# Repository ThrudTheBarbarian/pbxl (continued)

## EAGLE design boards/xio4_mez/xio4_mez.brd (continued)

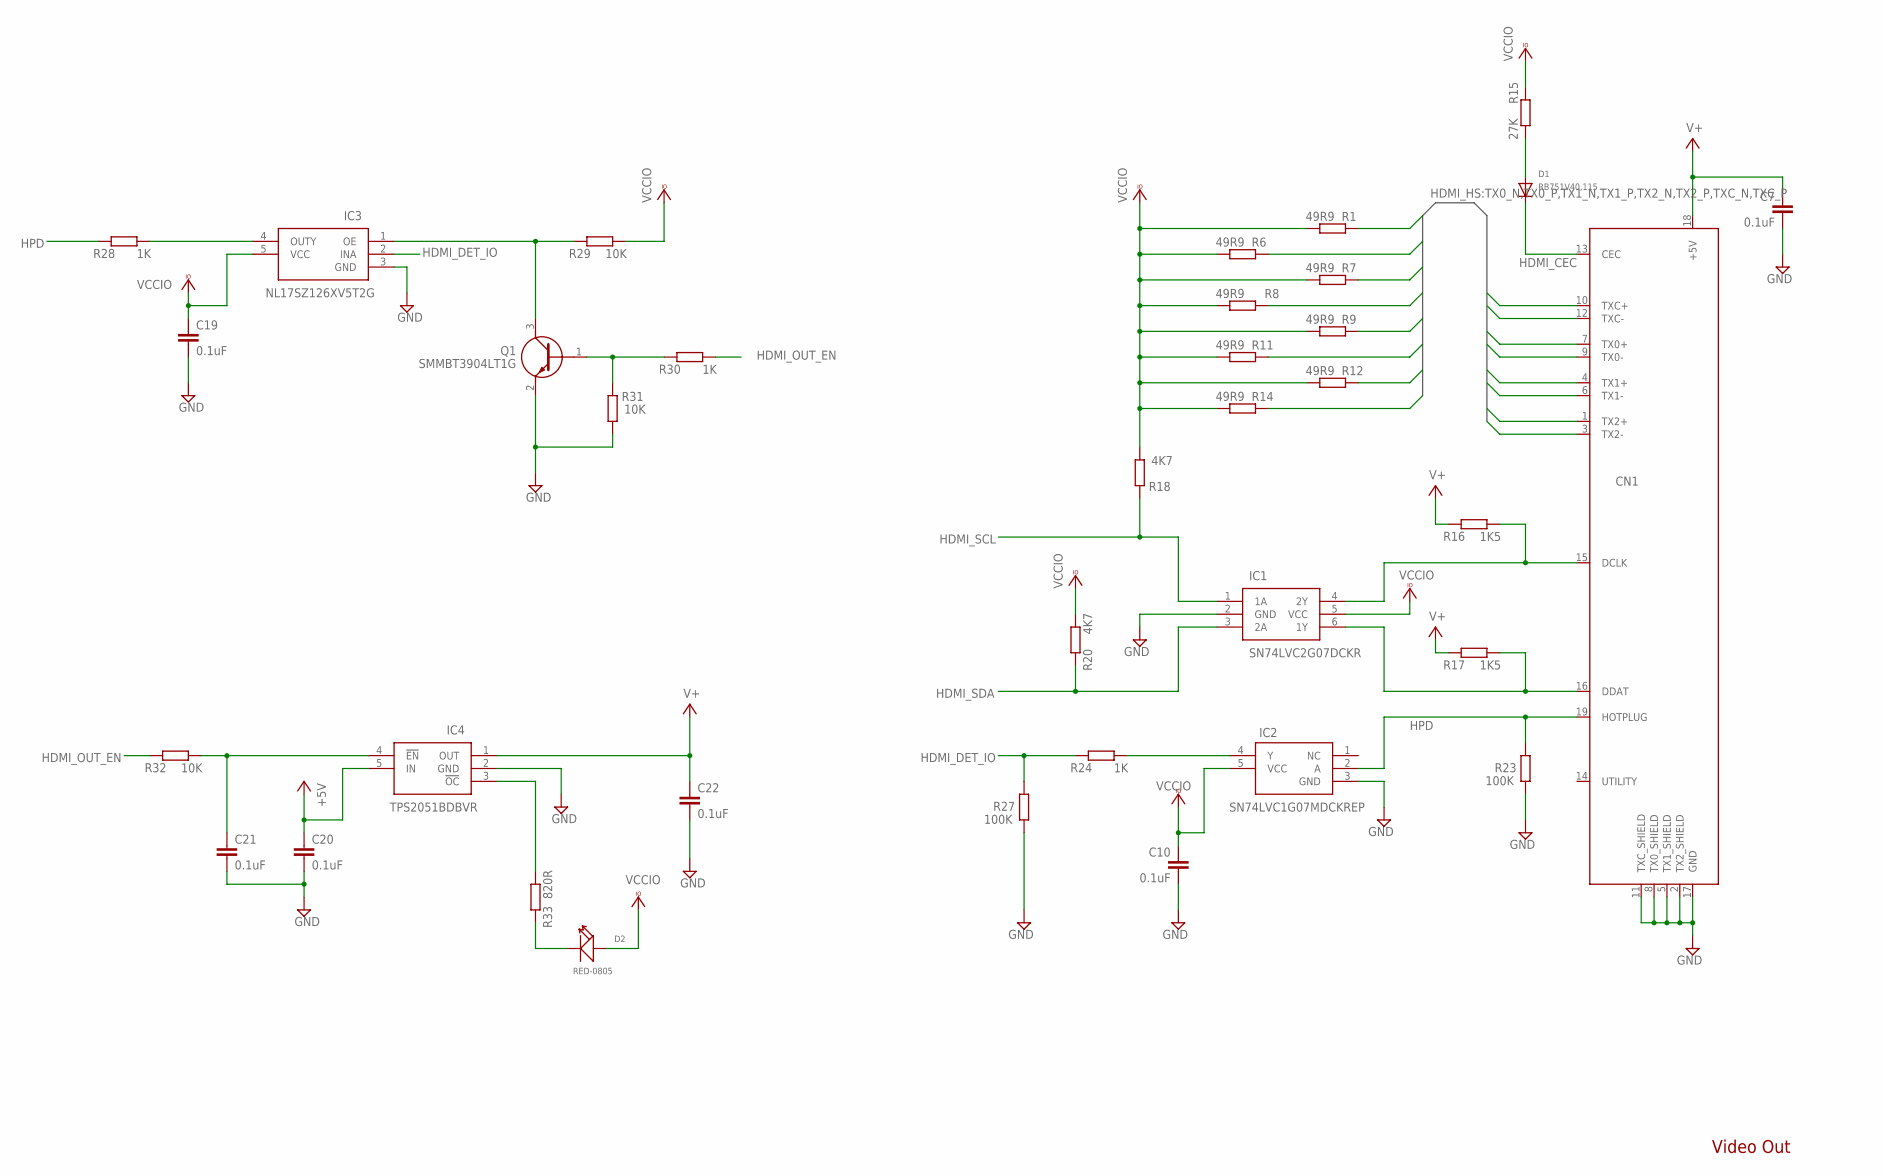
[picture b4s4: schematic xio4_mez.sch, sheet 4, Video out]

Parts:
C7, C10, C19, C20, C21, C22: 0.1uF; C0201
CN1: HDMI_MOLEX_47151-0001
D1: RB751V40,115; SOD-323
D2: RED-0805; LED-0805
IC1: SN74LVC2G07DCKR; SOT65P210X110X6N
IC2: SN74LVC1G07MDCKREP; SOT65P210X110-5N
IC3: NL17SZ126XV5T2G; SOTFL50P160X60-5N
IC4: TPS2051BDBVR; SOT95P280X145-5N
Q1: SMMBT3904LT1G; SOT96P237X111-3N
R1, R6, R7, R8, R9, R11, R12, R14: 49R9; R0201
R15: 27K; R0201
R16, R17: 1K5; R0201
R18, R20: 4K7; R0201
R23, R27: 100K; R0201
R24, R28, R30: 1K; R0201
R29, R31, R32: 10K; R0201
R33: 820R; R0201

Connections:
+5V: C20.1, IC4.5 (IN); also elsewhere on the board
GND: C7.2, C10.2, C19.2, C20.2, C21.2, C22.2, CN1.2 (TX2_SHIELD), CN1.5 (TX1_SHIELD), CN1.8 (TX0_SHIELD), CN1.11 (TXC_SHIELD), CN1.17 (GND), CN1.P$1 (GND), CN1.P$2 (GND), CN1.P$3 (GND), CN1.P$4 (GND), IC1.2 (GND), IC2.3 (GND), IC3.3 (GND), IC4.2 (GND), Q1.2 (E), R23.1, R27.1, R31.2; also elsewhere on the board
HDMI_CEC: CN1.13 (CEC), D1.C
HDMI_DET_IO: IC3.2 (INA), R24.2, R27.2; also elsewhere on the board
HDMI_OUT_EN: R30.1, R32.2; also elsewhere on the board
HDMI_SCL: IC1.1 (1A), R18.2; also elsewhere on the board
HDMI_SDA: IC1.3 (2A), R20.2; also elsewhere on the board
HPD: CN1.19 (HOTPLUG), IC2.2 (A), R23.2, R28.2
unnamed: CN1.16 (DDAT), IC1.6 (1Y), R17.1
unnamed: D1.A, R15.1
unnamed: CN1.15 (DCLK), IC1.4 (2Y), R16.1
unnamed: IC3.1 (OE), Q1.3 (C), R29.2
unnamed: IC2.4 (Y), R24.1
unnamed: IC3.4 (OUTY), R28.1
unnamed: Q1.1 (B), R30.2, R31.1
unnamed: C21.1, IC4.4 (!EN), R32.1
unnamed: IC4.3 (!OC), R33.1
unnamed: D2.-, R33.2
TX0_N: CN1.9 (TX0-), R1.2; also elsewhere on the board
TX0_P: CN1.7 (TX0+), R6.2; also elsewhere on the board
TX1_N: CN1.6 (TX1-), R7.2; also elsewhere on the board
TX1_P: CN1.4 (TX1+), R8.2; also elsewhere on the board
TX2_N: CN1.3 (TX2-), R9.2; also elsewhere on the board
TX2_P: CN1.1 (TX2+), R11.2; also elsewhere on the board
TXC_N: CN1.12 (TXC-), R12.2; also elsewhere on the board
TXC_P: CN1.10 (TXC+), R14.2; also elsewhere on the board
V+: C7.1, C22.1, CN1.18 (+5V), IC4.1 (OUT), R16.2, R17.2
VCCIO: C10.1, C19.1, D2.+, IC1.5 (VCC), IC2.5 (VCC), IC3.5 (VCC), R1.1, R6.1, R7.1, R8.1, R9.1, R11.1, R12.1, R14.1, R15.2, R18.1, R20.1, R29.1; also elsewhere on the board

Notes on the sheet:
Video Out

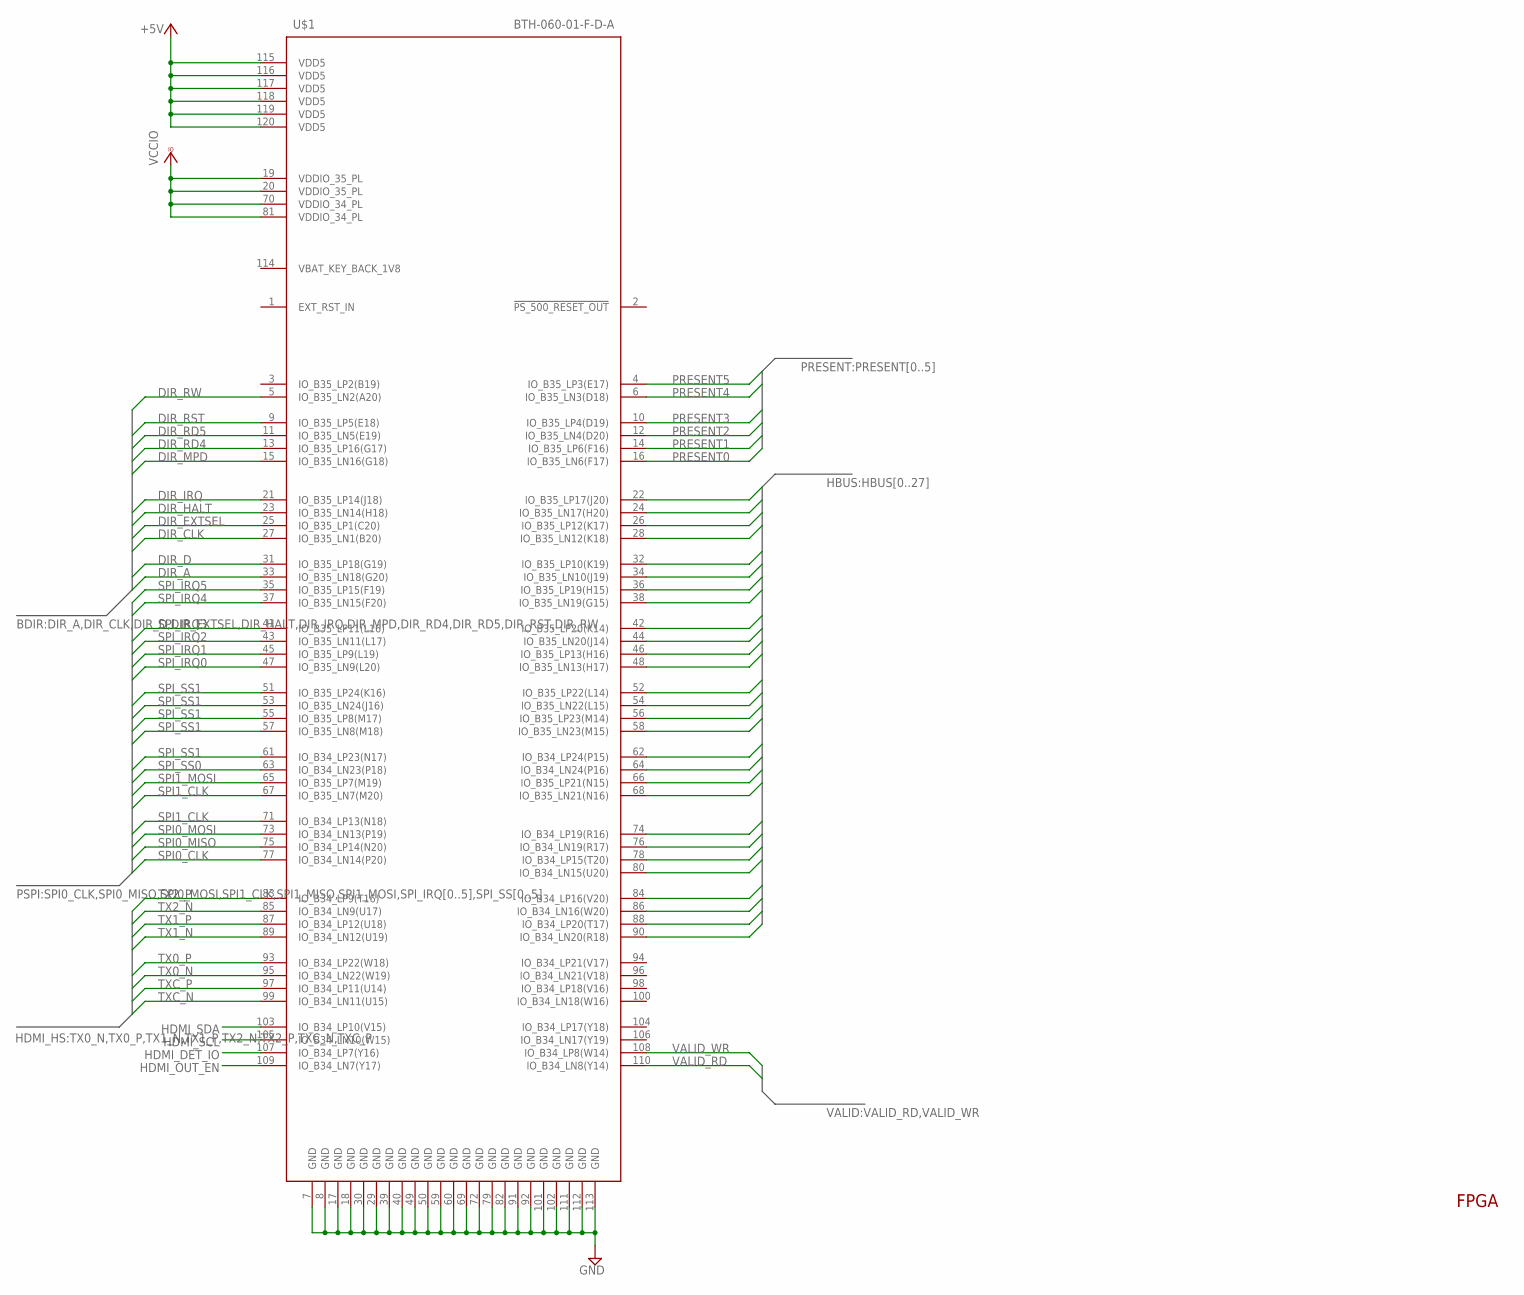
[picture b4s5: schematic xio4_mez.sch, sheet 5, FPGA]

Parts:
U$1: BTH-060-01-F-D-A

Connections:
+5V: U$1.115 (VDD5), U$1.116 (VDD5), U$1.117 (VDD5), U$1.118 (VDD5), U$1.119 (VDD5), U$1.120 (VDD5); also elsewhere on the board
DIR_A: U$1.33 (IO_B35_LN18(G20)); also elsewhere on the board
DIR_CLK: U$1.27 (IO_B35_LN1(B20)); also elsewhere on the board
DIR_D: U$1.31 (IO_B35_LP18(G19)); also elsewhere on the board
DIR_EXTSEL: U$1.25 (IO_B35_LP1(C20)); also elsewhere on the board
DIR_HALT: U$1.23 (IO_B35_LN14(H18)); also elsewhere on the board
DIR_IRQ: U$1.21 (IO_B35_LP14(J18)); also elsewhere on the board
DIR_MPD: U$1.15 (IO_B35_LN16(G18)); also elsewhere on the board
DIR_RD4: U$1.13 (IO_B35_LP16(G17)); also elsewhere on the board
DIR_RD5: U$1.11 (IO_B35_LN5(E19)); also elsewhere on the board
DIR_RST: U$1.9 (IO_B35_LP5(E18)); also elsewhere on the board
DIR_RW: U$1.5 (IO_B35_LN2(A20)); also elsewhere on the board
GND: U$1.7 (GND), U$1.8 (GND), U$1.17 (GND), U$1.18 (GND), U$1.29 (GND), U$1.30 (GND), U$1.39 (GND), U$1.40 (GND), U$1.49 (GND), U$1.50 (GND), U$1.59 (GND), U$1.60 (GND), U$1.69 (GND), U$1.72 (GND), U$1.79 (GND), U$1.82 (GND), U$1.91 (GND), U$1.92 (GND), U$1.101 (GND), U$1.102 (GND), U$1.111 (GND), U$1.112 (GND), U$1.113 (GND); also elsewhere on the board
HBUS0: U$1.22 (IO_B35_LP17(J20)); also elsewhere on the board
HBUS1: U$1.24 (IO_B35_LN17(H20)); also elsewhere on the board
HBUS2: U$1.26 (IO_B35_LP12(K17)); also elsewhere on the board
HBUS3: U$1.28 (IO_B35_LN12(K18)); also elsewhere on the board
HBUS4: U$1.32 (IO_B35_LP10(K19)); also elsewhere on the board
HBUS5: U$1.34 (IO_B35_LN10(J19)); also elsewhere on the board
HBUS6: U$1.36 (IO_B35_LP19(H15)); also elsewhere on the board
HBUS7: U$1.38 (IO_B35_LN19(G15)); also elsewhere on the board
HBUS8: U$1.42 (IO_B35_LP20(K14)); also elsewhere on the board
HBUS9: U$1.44 (IO_B35_LN20(J14)); also elsewhere on the board
HBUS10: U$1.46 (IO_B35_LP13(H16)); also elsewhere on the board
HBUS11: U$1.48 (IO_B35_LN13(H17)); also elsewhere on the board
HBUS12: U$1.52 (IO_B35_LP22(L14)); also elsewhere on the board
HBUS13: U$1.54 (IO_B35_LN22(L15)); also elsewhere on the board
HBUS14: U$1.56 (IO_B35_LP23(M14)); also elsewhere on the board
HBUS15: U$1.58 (IO_B35_LN23(M15)); also elsewhere on the board
HBUS16: U$1.62 (IO_B34_LP24(P15)); also elsewhere on the board
HBUS17: U$1.64 (IO_B34_LN24(P16)); also elsewhere on the board
HBUS18: U$1.66 (IO_B35_LP21(N15)); also elsewhere on the board
HBUS19: U$1.68 (IO_B35_LN21(N16)); also elsewhere on the board
HBUS20: U$1.74 (IO_B34_LP19(R16)); also elsewhere on the board
HBUS21: U$1.76 (IO_B34_LN19(R17)); also elsewhere on the board
HBUS22: U$1.78 (IO_B34_LP15(T20)); also elsewhere on the board
HBUS23: U$1.80 (IO_B34_LN15(U20)); also elsewhere on the board
HBUS24: U$1.84 (IO_B34_LP16(V20)); also elsewhere on the board
HBUS25: U$1.86 (IO_B34_LN16(W20)); also elsewhere on the board
HBUS26: U$1.88 (IO_B34_LP20(T17)); also elsewhere on the board
HBUS27: U$1.90 (IO_B34_LN20(R18)); also elsewhere on the board
HDMI_DET_IO: U$1.107 (IO_B34_LP7(Y16)); also elsewhere on the board
HDMI_OUT_EN: U$1.109 (IO_B34_LN7(Y17)); also elsewhere on the board
HDMI_SCL: U$1.105 (IO_B34_LN10(W15)); also elsewhere on the board
HDMI_SDA: U$1.103 (IO_B34_LP10(V15)); also elsewhere on the board
PRESENT0: U$1.16 (IO_B35_LN6(F17)); also elsewhere on the board
PRESENT1: U$1.14 (IO_B35_LP6(F16)); also elsewhere on the board
PRESENT2: U$1.12 (IO_B35_LN4(D20)); also elsewhere on the board
PRESENT3: U$1.10 (IO_B35_LP4(D19)); also elsewhere on the board
PRESENT4: U$1.6 (IO_B35_LN3(D18)); also elsewhere on the board
PRESENT5: U$1.4 (IO_B35_LP3(E17)); also elsewhere on the board
SPI0_CLK: U$1.77 (IO_B34_LN14(P20)); also elsewhere on the board
SPI0_MISO: U$1.75 (IO_B34_LP14(N20)); also elsewhere on the board
SPI0_MOSI: U$1.73 (IO_B34_LN13(P19)); also elsewhere on the board
SPI1_CLK: U$1.71 (IO_B34_LP13(N18)); also elsewhere on the board
SPI1_MISO: U$1.67 (IO_B35_LN7(M20)); also elsewhere on the board
SPI1_MOSI: U$1.65 (IO_B35_LP7(M19)); also elsewhere on the board
SPI_IRQ0: U$1.47 (IO_B35_LN9(L20)); also elsewhere on the board
SPI_IRQ1: U$1.45 (IO_B35_LP9(L19)); also elsewhere on the board
SPI_IRQ2: U$1.43 (IO_B35_LN11(L17)); also elsewhere on the board
SPI_IRQ3: U$1.41 (IO_B35_LP11(L16)); also elsewhere on the board
SPI_IRQ4: U$1.37 (IO_B35_LN15(F20)); also elsewhere on the board
SPI_IRQ5: U$1.35 (IO_B35_LP15(F19)); also elsewhere on the board
SPI_SS0: U$1.63 (IO_B34_LN23(P18)); also elsewhere on the board
SPI_SS1: U$1.61 (IO_B34_LP23(N17)); also elsewhere on the board
SPI_SS2: U$1.57 (IO_B35_LN8(M18)); also elsewhere on the board
SPI_SS3: U$1.55 (IO_B35_LP8(M17)); also elsewhere on the board
SPI_SS4: U$1.53 (IO_B35_LN24(J16)); also elsewhere on the board
SPI_SS5: U$1.51 (IO_B35_LP24(K16)); also elsewhere on the board
TX0_N: U$1.95 (IO_B34_LN22(W19)); also elsewhere on the board
TX0_P: U$1.93 (IO_B34_LP22(W18)); also elsewhere on the board
TX1_N: U$1.89 (IO_B34_LN12(U19)); also elsewhere on the board
TX1_P: U$1.87 (IO_B34_LP12(U18)); also elsewhere on the board
TX2_N: U$1.85 (IO_B34_LN9(U17)); also elsewhere on the board
TX2_P: U$1.83 (IO_B34_LP9(T16)); also elsewhere on the board
TXC_N: U$1.99 (IO_B34_LN11(U15)); also elsewhere on the board
TXC_P: U$1.97 (IO_B34_LP11(U14)); also elsewhere on the board
VALID_RD: U$1.110 (IO_B34_LN8(Y14)); also elsewhere on the board
VALID_WR: U$1.108 (IO_B34_LP8(W14)); also elsewhere on the board
VCCIO: U$1.19 (VDDIO_35_PL), U$1.20 (VDDIO_35_PL), U$1.70 (VDDIO_34_PL), U$1.81 (VDDIO_34_PL); also elsewhere on the board

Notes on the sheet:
FPGA

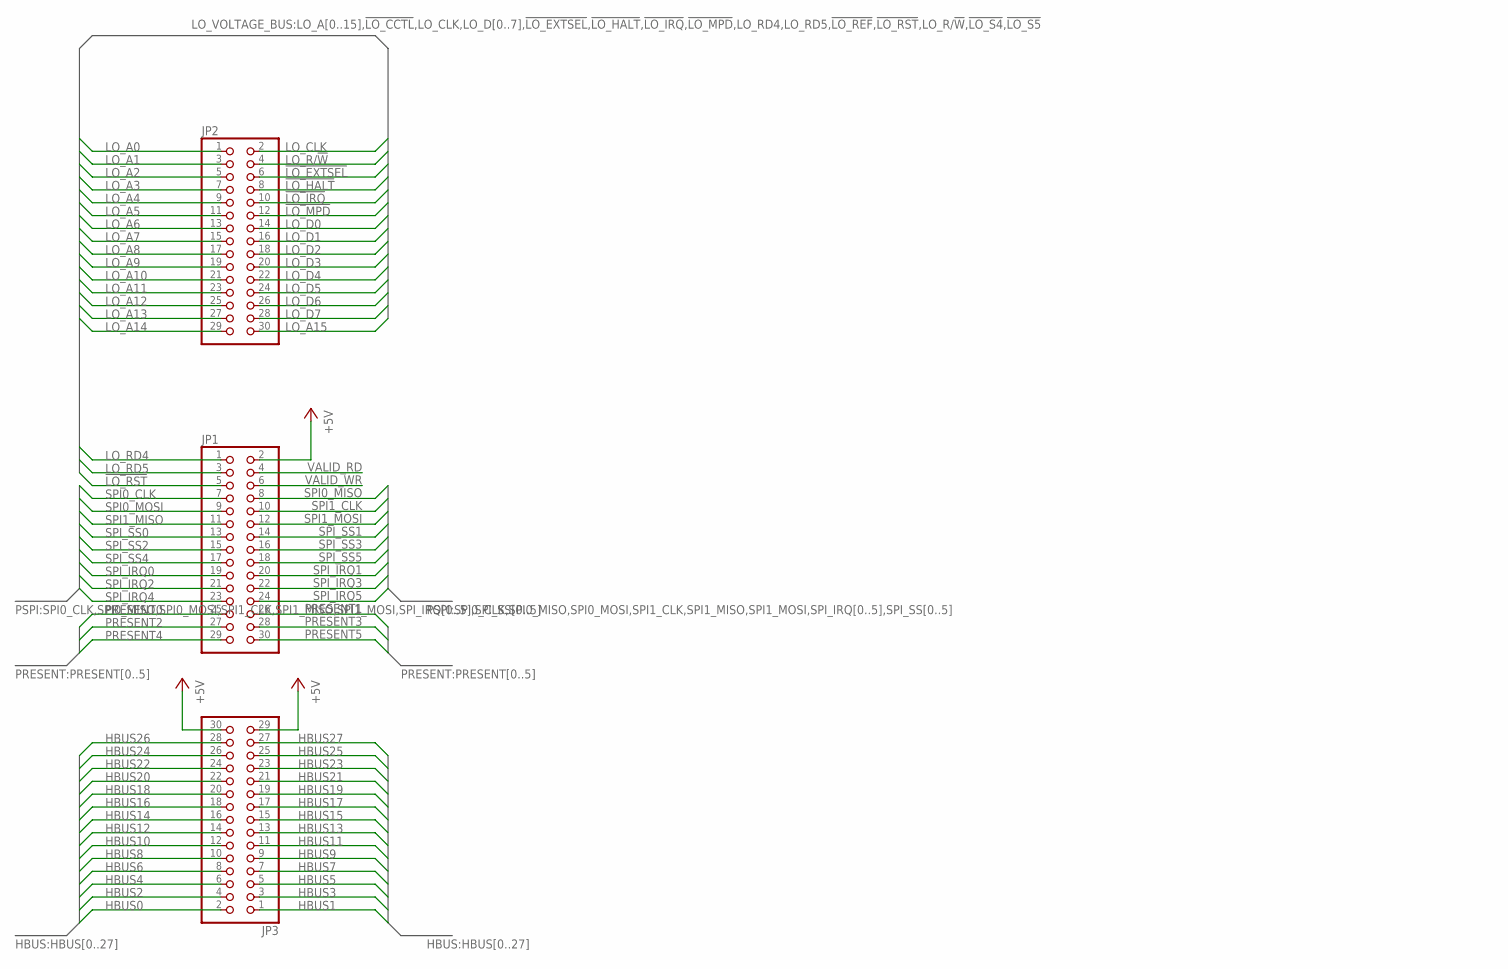
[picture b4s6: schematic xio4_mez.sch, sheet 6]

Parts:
JP1, JP2, JP3: PINHD-2X15_2.54-SMD; 2X15SMD

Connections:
!LO_EXTSEL!: JP2.6; also elsewhere on the board
!LO_HALT!: JP2.8; also elsewhere on the board
!LO_IRQ!: JP2.10; also elsewhere on the board
!LO_MPD!: JP2.12; also elsewhere on the board
!LO_RST!: JP1.5; also elsewhere on the board
+5V: JP1.2, JP3.29, JP3.30; also elsewhere on the board
HBUS0: JP3.2; also elsewhere on the board
HBUS1: JP3.1; also elsewhere on the board
HBUS2: JP3.4; also elsewhere on the board
HBUS3: JP3.3; also elsewhere on the board
HBUS4: JP3.6; also elsewhere on the board
HBUS5: JP3.5; also elsewhere on the board
HBUS6: JP3.8; also elsewhere on the board
HBUS7: JP3.7; also elsewhere on the board
HBUS8: JP3.10; also elsewhere on the board
HBUS9: JP3.9; also elsewhere on the board
HBUS10: JP3.12; also elsewhere on the board
HBUS11: JP3.11; also elsewhere on the board
HBUS12: JP3.14; also elsewhere on the board
HBUS13: JP3.13; also elsewhere on the board
HBUS14: JP3.16; also elsewhere on the board
HBUS15: JP3.15; also elsewhere on the board
HBUS16: JP3.18; also elsewhere on the board
HBUS17: JP3.17; also elsewhere on the board
HBUS18: JP3.20; also elsewhere on the board
HBUS19: JP3.19; also elsewhere on the board
HBUS20: JP3.22; also elsewhere on the board
HBUS21: JP3.21; also elsewhere on the board
HBUS22: JP3.24; also elsewhere on the board
HBUS23: JP3.23; also elsewhere on the board
HBUS24: JP3.26; also elsewhere on the board
HBUS25: JP3.25; also elsewhere on the board
HBUS26: JP3.28; also elsewhere on the board
HBUS27: JP3.27; also elsewhere on the board
LO_A0: JP2.1; also elsewhere on the board
LO_A1: JP2.3; also elsewhere on the board
LO_A2: JP2.5; also elsewhere on the board
LO_A3: JP2.7; also elsewhere on the board
LO_A4: JP2.9; also elsewhere on the board
LO_A5: JP2.11; also elsewhere on the board
LO_A6: JP2.13; also elsewhere on the board
LO_A7: JP2.15; also elsewhere on the board
LO_A8: JP2.17; also elsewhere on the board
LO_A9: JP2.19; also elsewhere on the board
LO_A10: JP2.21; also elsewhere on the board
LO_A11: JP2.23; also elsewhere on the board
LO_A12: JP2.25; also elsewhere on the board
LO_A13: JP2.27; also elsewhere on the board
LO_A14: JP2.29; also elsewhere on the board
LO_A15: JP2.30; also elsewhere on the board
LO_CLK: JP2.2; also elsewhere on the board
LO_D0: JP2.14; also elsewhere on the board
LO_D1: JP2.16; also elsewhere on the board
LO_D2: JP2.18; also elsewhere on the board
LO_D3: JP2.20; also elsewhere on the board
LO_D4: JP2.22; also elsewhere on the board
LO_D5: JP2.24; also elsewhere on the board
LO_D6: JP2.26; also elsewhere on the board
LO_D7: JP2.28; also elsewhere on the board
LO_R/!W!: JP2.4; also elsewhere on the board
LO_RD4: JP1.1; also elsewhere on the board
LO_RD5: JP1.3; also elsewhere on the board
PRESENT0: JP1.25; also elsewhere on the board
PRESENT1: JP1.26; also elsewhere on the board
PRESENT2: JP1.27; also elsewhere on the board
PRESENT3: JP1.28; also elsewhere on the board
PRESENT4: JP1.29; also elsewhere on the board
PRESENT5: JP1.30; also elsewhere on the board
SPI0_CLK: JP1.7; also elsewhere on the board
SPI0_MISO: JP1.8; also elsewhere on the board
SPI0_MOSI: JP1.9; also elsewhere on the board
SPI1_CLK: JP1.10; also elsewhere on the board
SPI1_MISO: JP1.11; also elsewhere on the board
SPI1_MOSI: JP1.12; also elsewhere on the board
SPI_IRQ0: JP1.19; also elsewhere on the board
SPI_IRQ1: JP1.20; also elsewhere on the board
SPI_IRQ2: JP1.21; also elsewhere on the board
SPI_IRQ3: JP1.22; also elsewhere on the board
SPI_IRQ4: JP1.23; also elsewhere on the board
SPI_IRQ5: JP1.24; also elsewhere on the board
SPI_SS0: JP1.13; also elsewhere on the board
SPI_SS1: JP1.14; also elsewhere on the board
SPI_SS2: JP1.15; also elsewhere on the board
SPI_SS3: JP1.16; also elsewhere on the board
SPI_SS4: JP1.17; also elsewhere on the board
SPI_SS5: JP1.18; also elsewhere on the board
VALID_RD: JP1.4; also elsewhere on the board
VALID_WR: JP1.6; also elsewhere on the board

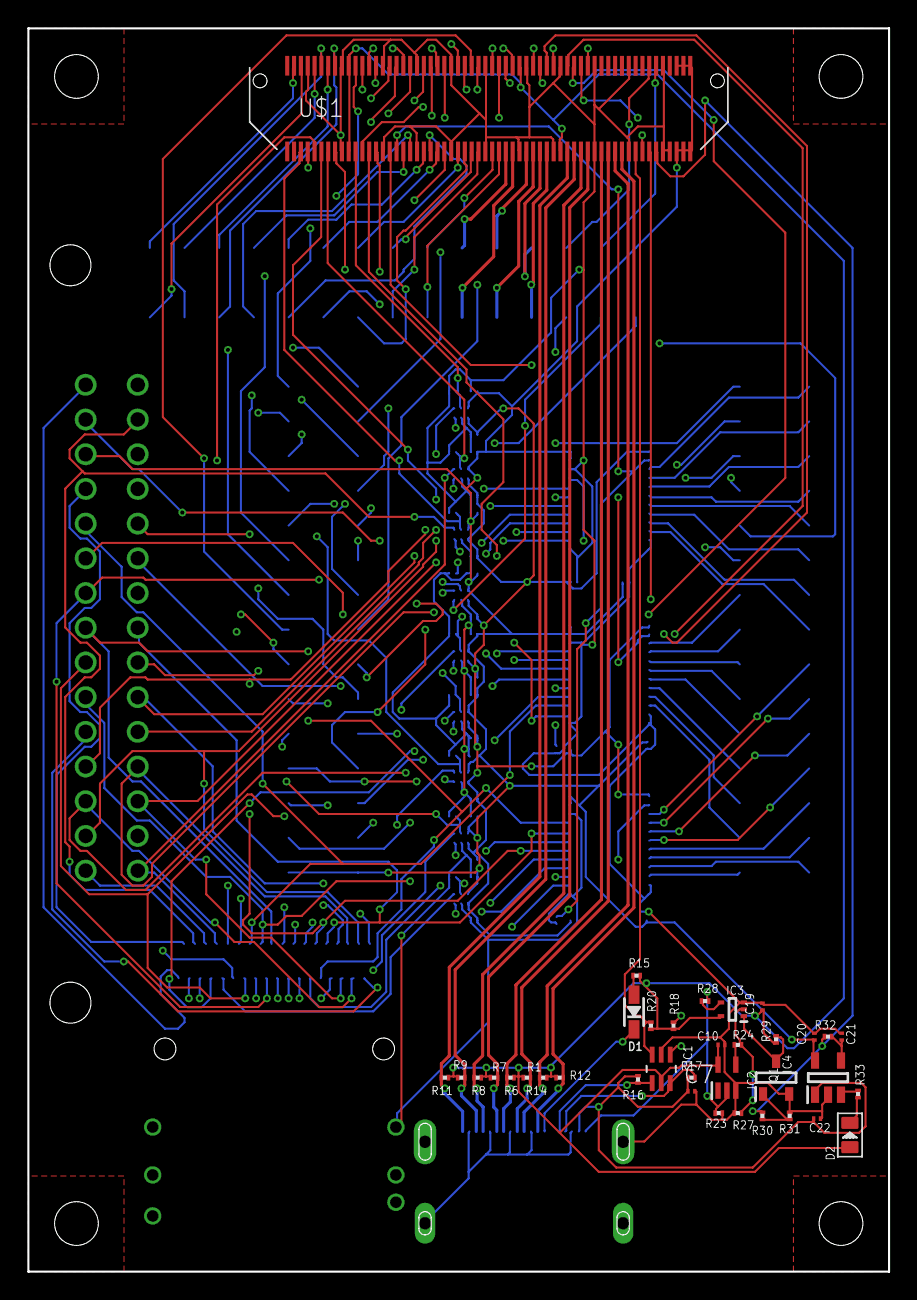
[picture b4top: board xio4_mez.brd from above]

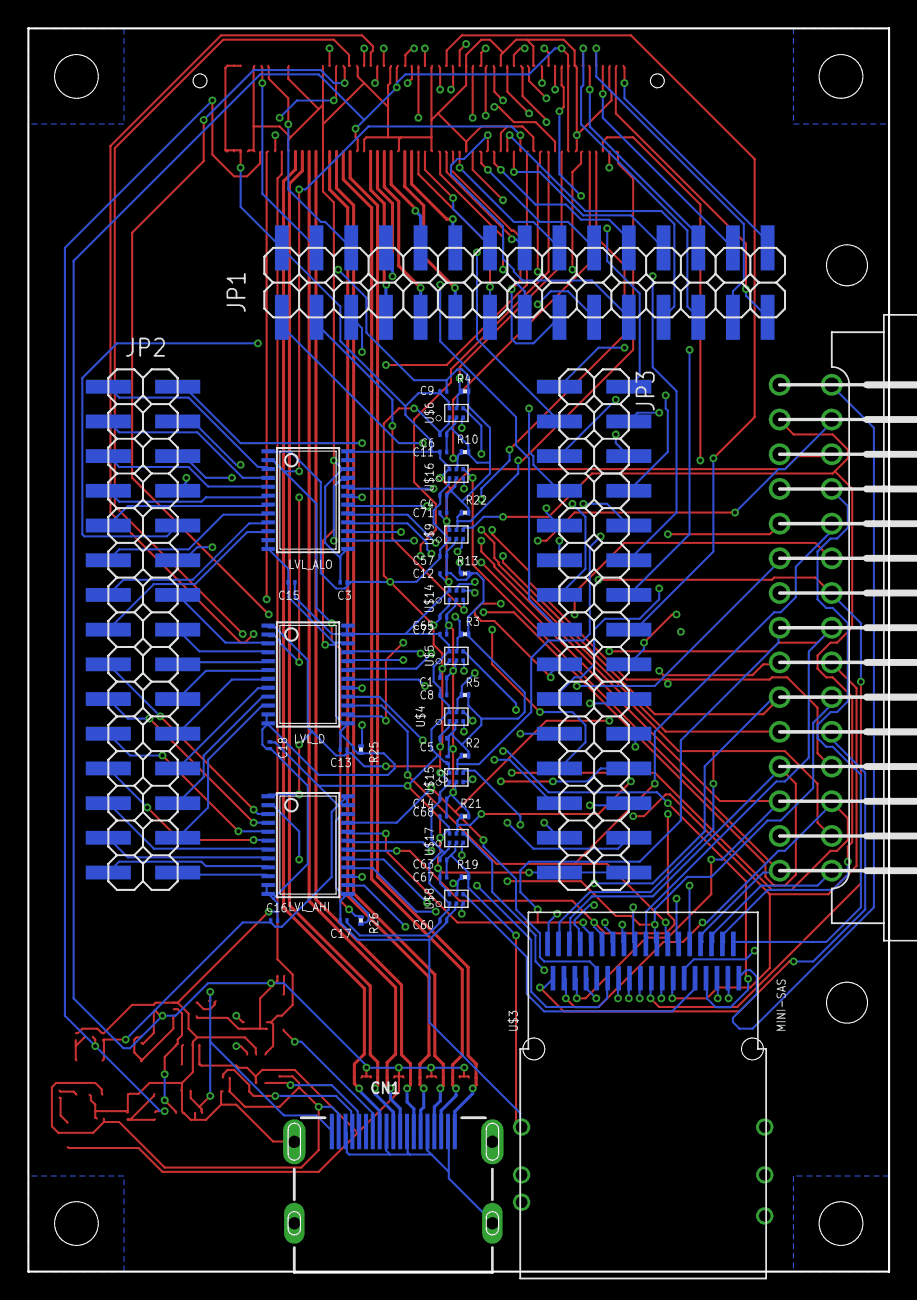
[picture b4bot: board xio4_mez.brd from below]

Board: 4 copper layers, 63.0 x 91.0 mm, 89 parts (53 on the bottom side), 163 nets.

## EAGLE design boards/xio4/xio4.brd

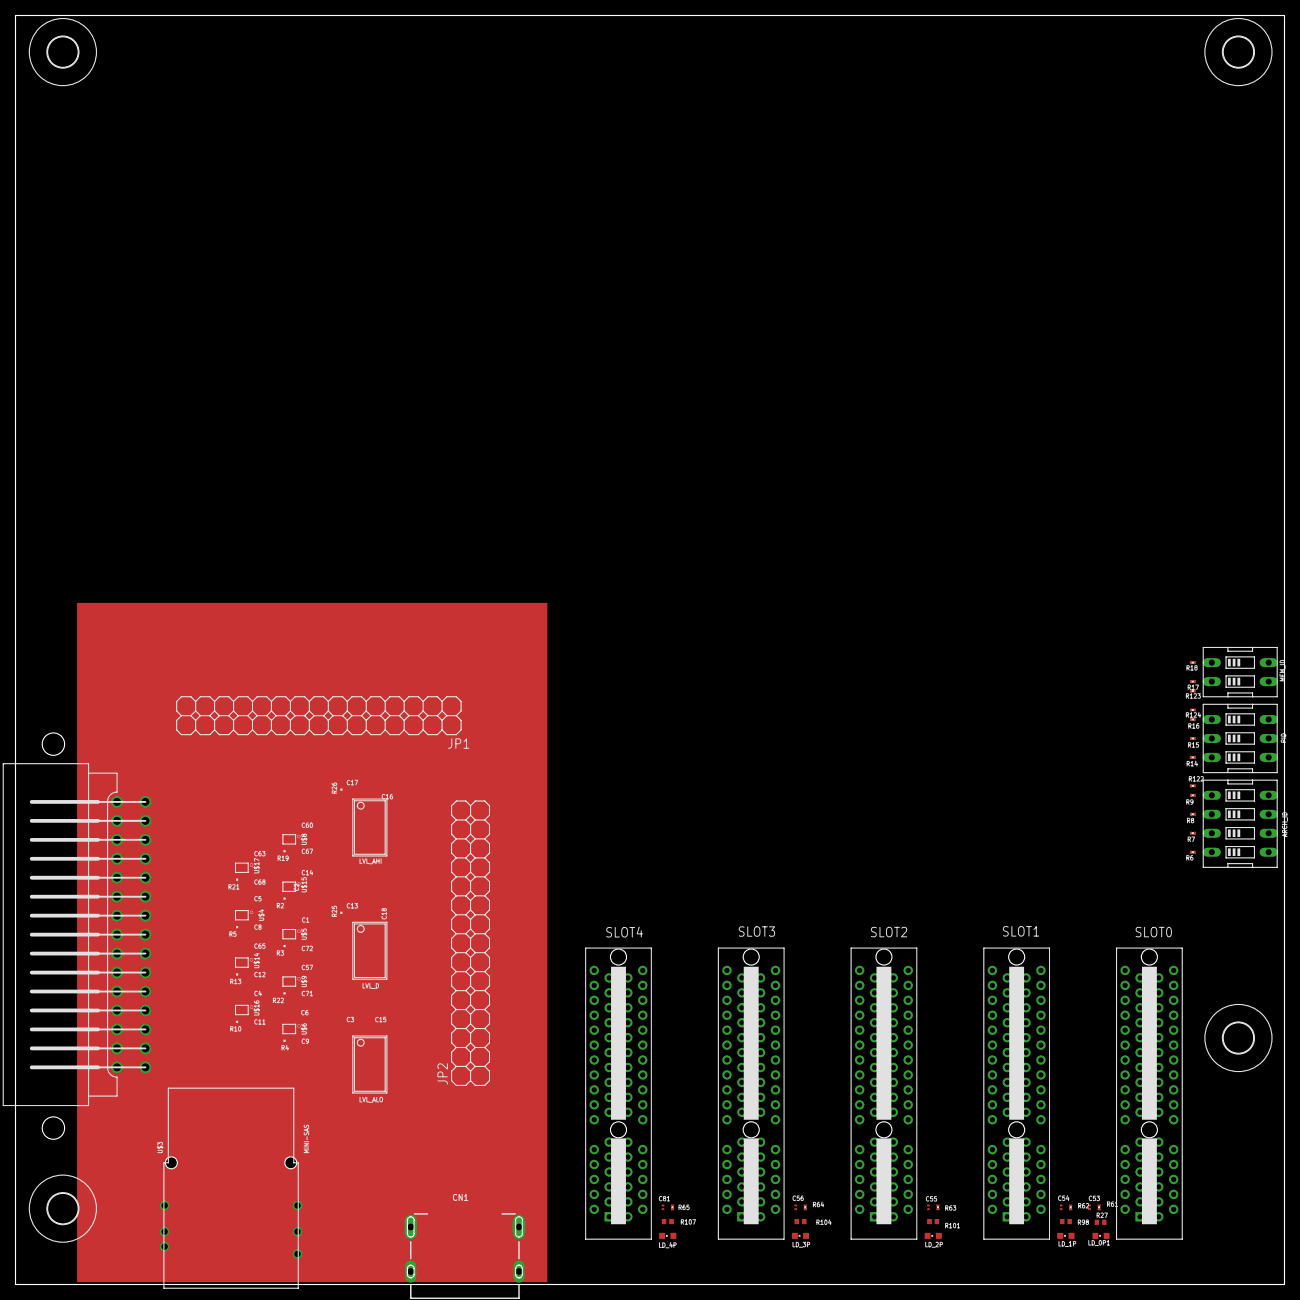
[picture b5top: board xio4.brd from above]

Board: 4 copper layers, 170.0 x 170.0 mm, 96 parts (0 on the bottom side), 123 nets, no tracks yet.

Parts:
ARCH_ID: 209-4MS; EDG-04
C1, C2, C3, C4, C5, C6, C8, C9, C11, C12, C13, C14, C15, C16, C17, C18, C53, C54, C55, C56, C57, C60, C63, C65, C67, C68, C71, C72, C81: 0.1uF; C0201
CARTRIDGE: 5650118-1; A8_CART
CN1: HDMI_MOLEX_47151-0001
H3, H6, H7, H8: MOUNT-HOLE4.1; 4,1
JP1, JP2: 2X15SMD
LD_0P1, LD_1P, LD_2P, LD_3P, LD_4P: SML-D12D1WT86; CHIPLED_0603
LVL_AHI: SN74LVC8T245; TSSOP24
LVL_ALO: SN74LVC8T245; TSSOP24
LVL_D: SN74LVC8T245; TSSOP24
MEM_ID: 209-2MS; EDG-02
PID: 209-3MS; EDG-03
R2, R3, R4, R5, R10, R13, R19, R21, R22, R25, R26, R61, R62, R63, R64, R65: 10K; R0201
R6, R7, R8, R9, R14, R15, R16, R17, R18: 47K; R0201
R27, R98, R101, R104, R107: 59R; R0402
R122, R123, R124: 1K; R0201
SLOT0, SLOT1, SLOT2, SLOT3, SLOT4: PCIE_64; PCI-E_64
U$3: MINI-SAS
U$4, U$5, U$6, U$8, U$9, U$14, U$15, U$16, U$17: 74LVC1T45GWSOT866; SOT886

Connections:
!HI_CCTL!: CARTRIDGE.P15, U$3.PA18
!HI_EXTSEL!: U$3.PB13, U$5.4
!HI_HALT!: U$3.PA14, U$8.4
!HI_IRQ!: U$3.PB14, U$6.4
!HI_MPD!: U$3.PA15, U$4.4
!HI_RST!: U$3.PA17, U$17.4
!HI_S4!: CARTRIDGE.P1, U$3.PB16
!HI_S5!: CARTRIDGE.P12, U$3.PB18
!LO_CCTL!: SLOT0.A27, SLOT1.A27, SLOT2.A27, SLOT3.A27, SLOT4.A27
!LO_EXTSEL!: SLOT0.A29, SLOT1.A29, SLOT2.A29, SLOT3.A29, SLOT4.A29, U$5.3
!LO_HALT!: SLOT0.B13, SLOT1.B13, SLOT2.B13, SLOT3.B13, SLOT4.B13, U$8.3
!LO_IRQ!: SLOT0.B14, SLOT1.B14, SLOT2.B14, SLOT3.B14, SLOT4.B14, U$6.3
!LO_MPD!: SLOT0.A30, SLOT1.A30, SLOT2.A30, SLOT3.A30, SLOT4.A30, U$4.3
!LO_REF!: SLOT0.B15, SLOT1.B15, SLOT2.B15, SLOT3.B15, SLOT4.B15
!LO_RST!: SLOT0.B16, SLOT1.B16, SLOT2.B16, SLOT3.B16, SLOT4.B16, U$17.3
+3V3: C1.1, C3.1, C4.1, C5.1, C6.1, C13.1, C14.1, C17.1, C57.1, C60.1, C63.1, C65.1, LVL_AHI.1, LVL_ALO.1, LVL_D.1, R122.1, R123.1, R124.1, SLOT1.A3, SLOT2.A2, SLOT3.A2, SLOT3.A3, SLOT4.A1, U$4.1, U$5.1, U$6.1, U$8.1, U$9.1, U$14.1, U$15.1, U$16.1, U$17.1
+5V: C2.1, C8.1, C9.1, C11.1, C12.1, C15.1, C16.1, C18.1, C53.1, C54.1, C55.1, C56.1, C67.1, C68.1, C71.1, C72.1, C81.1, CARTRIDGE.P13, CN1.18, LVL_AHI.23, LVL_AHI.24, LVL_ALO.23, LVL_ALO.24, LVL_D.23, LVL_D.24, SLOT0.B1, SLOT0.B2, SLOT0.B3, SLOT1.B1, SLOT1.B2, SLOT1.B3, SLOT2.B1, SLOT2.B2, SLOT2.B3, SLOT3.B1, SLOT3.B2, SLOT3.B3, SLOT4.B1, SLOT4.B2, SLOT4.B3, U$4.6, U$5.6, U$6.6, U$8.6, U$9.6, U$14.6, U$15.6, U$16.6, U$17.6
ARCH0: ARCH_ID.1, R9.1
ARCH1: ARCH_ID.2, R8.1
ARCH2: ARCH_ID.3, R7.1
ARCH3: ARCH_ID.4, R6.1
DIR_A: LVL_AHI.2, LVL_ALO.2, R26.1
DIR_CLK: R2.1, U$15.5
DIR_D: LVL_D.2, R25.1
DIR_EXTSEL: R3.1, U$5.5
DIR_HALT: R19.1, U$8.5
DIR_IRQ: R4.1, U$6.5
DIR_MPD: R5.1, U$4.5
DIR_RD4: R10.1, U$16.5
DIR_RD5: R13.1, U$14.5
DIR_RST: R21.1, U$17.5
DIR_RW: R22.1, U$9.5
GND: C1.2, C2.2, C3.2, C4.2, C5.2, C6.2, C8.2, C9.2, C11.2, C12.2, C13.2, C14.2, C15.2, C16.2, C17.2, C18.2, C53.2, C54.2, C55.2, C56.2, C57.2, C60.2, C63.2, C65.2, C67.2, C68.2, C71.2, C72.2, C81.2, CARTRIDGE.PB, CN1.17, CN1.P$1, CN1.P$2, CN1.P$3, CN1.P$4, LD_0P1.C, LD_1P.C, LD_2P.C, LD_3P.C, LD_4P.C, LVL_AHI.11, LVL_AHI.12, LVL_AHI.13, LVL_AHI.22, LVL_ALO.11, LVL_ALO.12, LVL_ALO.13, LVL_ALO.22, LVL_D.11, LVL_D.12, LVL_D.13, LVL_D.22, R2.2, R3.2, R4.2, R5.2, R6.2, R7.2, R8.2, R9.2, R10.2, R13.2, R14.2, R15.2, R16.2, R17.2, R18.2, R19.2, R21.2, R22.2, R25.2, R26.2, R61.1, R62.1, R63.1, R64.1, R65.1, SLOT0.A1, SLOT0.A2, SLOT0.A3, SLOT0.A4, SLOT0.A5, SLOT0.B32, SLOT1.A1, SLOT1.A2, SLOT1.A4, SLOT1.A5, SLOT1.B32, SLOT2.A1, SLOT2.A3, SLOT2.A4, SLOT2.A5, SLOT2.B32, SLOT3.A1, SLOT3.A4, SLOT3.A5, SLOT3.B32, SLOT4.A2, SLOT4.A3, SLOT4.A4, SLOT4.A5, SLOT4.B32, U$3.SHIELD1, U$3.SHIELD2, U$3.SHIELD3, U$3.SHIELD4, U$3.SHIELD5, U$3.SHIELD6, U$4.2, U$5.2, U$6.2, U$8.2, U$9.2, U$14.2, U$15.2, U$16.2, U$17.2
HBUS0: SLOT0.B18, SLOT1.B18, SLOT2.B18, SLOT3.B18, SLOT4.B18
HBUS1: SLOT0.B19, SLOT1.B19, SLOT2.B19, SLOT3.B19, SLOT4.B19
HBUS2: SLOT0.B20, SLOT1.B20, SLOT2.B20, SLOT3.B20, SLOT4.B20
HBUS3: SLOT0.B21, SLOT1.B21, SLOT2.B21, SLOT3.B21, SLOT4.B21
HBUS4: SLOT0.B22, SLOT1.B22, SLOT2.B22, SLOT3.B22, SLOT4.B22
HBUS5: SLOT0.B23, SLOT1.B23, SLOT2.B23, SLOT3.B23, SLOT4.B23
HBUS6: SLOT0.B24, SLOT1.B24, SLOT2.B24, SLOT3.B24, SLOT4.B24
HBUS7: SLOT0.B25, SLOT1.B25, SLOT2.B25, SLOT3.B25, SLOT4.B25
HBUS8: SLOT0.B26, SLOT1.B26, SLOT2.B26, SLOT3.B26, SLOT4.B26
HBUS9: SLOT0.B27, SLOT1.B27, SLOT2.B27, SLOT3.B27, SLOT4.B27
HBUS10: SLOT0.B28, SLOT1.B28, SLOT2.B28, SLOT3.B28, SLOT4.B28
HBUS11: SLOT0.B29, SLOT1.B29, SLOT2.B29, SLOT3.B29, SLOT4.B29
HBUS12: SLOT0.B30, SLOT1.B30, SLOT2.B30, SLOT3.B30, SLOT4.B30
HBUS13: SLOT0.B31, SLOT1.B31, SLOT2.B31, SLOT3.B31, SLOT4.B31
HI_A0: CARTRIDGE.P5, LVL_ALO.21, U$3.PA1
HI_A1: CARTRIDGE.P4, LVL_ALO.20, U$3.PB1
HI_A2: CARTRIDGE.P3, LVL_ALO.19, U$3.PA2
HI_A3: CARTRIDGE.P2, LVL_ALO.18, U$3.PB2
HI_A4: CARTRIDGE.PC, LVL_ALO.17, U$3.PA3
HI_A5: CARTRIDGE.PD, LVL_ALO.16, U$3.PB3
HI_A6: CARTRIDGE.PE, LVL_ALO.15, U$3.PA4
HI_A7: CARTRIDGE.PF, LVL_ALO.14, U$3.PB4
HI_A8: CARTRIDGE.PH, LVL_AHI.21, U$3.PA5
HI_A9: CARTRIDGE.PJ, LVL_AHI.20, U$3.PB5
HI_A10: CARTRIDGE.PP, LVL_AHI.19, U$3.PA6
HI_A11: CARTRIDGE.PN, LVL_AHI.18, U$3.PB6
HI_A12: CARTRIDGE.PK, LVL_AHI.17, U$3.PA7
HI_A13: LVL_AHI.16, U$3.PB7
HI_A14: LVL_AHI.15, U$3.PA8
HI_A15: LVL_AHI.14, U$3.PB8
HI_CLK: CARTRIDGE.PS, U$3.PA9, U$15.4
HI_D0: CARTRIDGE.P10, LVL_D.21, U$3.PB9
HI_D1: CARTRIDGE.P9, LVL_D.20, U$3.PA10
HI_D2: CARTRIDGE.P8, LVL_D.19, U$3.PB10
HI_D3: CARTRIDGE.PL, LVL_D.18, U$3.PA11
HI_D4: CARTRIDGE.P6, LVL_D.17, U$3.PB11
HI_D5: CARTRIDGE.P7, LVL_D.16, U$3.PA12
HI_D6: CARTRIDGE.P11, LVL_D.15, U$3.PB12
HI_D7: CARTRIDGE.PM, LVL_D.14, U$3.PA13
HI_R/!W!: CARTRIDGE.PR, U$3.PB17, U$9.4
HI_RD4: CARTRIDGE.PA, U$3.PB15, U$16.4
HI_RD5: CARTRIDGE.P14, U$3.PA16, U$14.4
LO_A0: LVL_ALO.3, SLOT0.A11, SLOT1.A11, SLOT2.A11, SLOT3.A11, SLOT4.A11
LO_A1: LVL_ALO.4, SLOT0.A12, SLOT1.A12, SLOT2.A12, SLOT3.A12, SLOT4.A12
LO_A2: LVL_ALO.5, SLOT0.A13, SLOT1.A13, SLOT2.A13, SLOT3.A13, SLOT4.A13
LO_A3: LVL_ALO.6, SLOT0.A14, SLOT1.A14, SLOT2.A14, SLOT3.A14, SLOT4.A14
LO_A4: LVL_ALO.7, SLOT0.A15, SLOT1.A15, SLOT2.A15, SLOT3.A15, SLOT4.A15
LO_A5: LVL_ALO.8, SLOT0.A16, SLOT1.A16, SLOT2.A16, SLOT3.A16, SLOT4.A16
LO_A6: LVL_ALO.9, SLOT0.A17, SLOT1.A17, SLOT2.A17, SLOT3.A17, SLOT4.A17
LO_A7: LVL_ALO.10, SLOT0.A18, SLOT1.A18, SLOT2.A18, SLOT3.A18, SLOT4.A18
LO_A8: LVL_AHI.3, SLOT0.A19, SLOT1.A19, SLOT2.A19, SLOT3.A19, SLOT4.A19
LO_A9: LVL_AHI.4, SLOT0.A20, SLOT1.A20, SLOT2.A20, SLOT3.A20, SLOT4.A20
LO_A10: LVL_AHI.5, SLOT0.A21, SLOT1.A21, SLOT2.A21, SLOT3.A21, SLOT4.A21
LO_A11: LVL_AHI.6, SLOT0.A22, SLOT1.A22, SLOT2.A22, SLOT3.A22, SLOT4.A22
LO_A12: LVL_AHI.7, SLOT0.A23, SLOT1.A23, SLOT2.A23, SLOT3.A23, SLOT4.A23
LO_A13: LVL_AHI.8, SLOT0.A24, SLOT1.A24, SLOT2.A24, SLOT3.A24, SLOT4.A24
LO_A14: LVL_AHI.9, SLOT0.A25, SLOT1.A25, SLOT2.A25, SLOT3.A25, SLOT4.A25
LO_A15: LVL_AHI.10, SLOT0.A26, SLOT1.A26, SLOT2.A26, SLOT3.A26, SLOT4.A26
LO_CLK: SLOT0.A28, SLOT1.A28, SLOT2.A28, SLOT3.A28, SLOT4.A28, U$15.3
LO_D0: LVL_D.3, SLOT0.B5, SLOT1.B5, SLOT2.B5, SLOT3.B5, SLOT4.B5
LO_D1: LVL_D.4, SLOT0.B6, SLOT1.B6, SLOT2.B6, SLOT3.B6, SLOT4.B6
LO_D2: LVL_D.5, SLOT0.B7, SLOT1.B7, SLOT2.B7, SLOT3.B7, SLOT4.B7
LO_D3: LVL_D.6, SLOT0.B8, SLOT1.B8, SLOT2.B8, SLOT3.B8, SLOT4.B8
LO_D4: LVL_D.7, SLOT0.B9, SLOT1.B9, SLOT2.B9, SLOT3.B9, SLOT4.B9
LO_D5: LVL_D.8, SLOT0.B10, SLOT1.B10, SLOT2.B10, SLOT3.B10, SLOT4.B10
LO_D6: LVL_D.9, SLOT0.B11, SLOT1.B11, SLOT2.B11, SLOT3.B11, SLOT4.B11
LO_D7: LVL_D.10, SLOT0.B12, SLOT1.B12, SLOT2.B12, SLOT3.B12, SLOT4.B12
LO_R/!W!: SLOT0.B17, SLOT1.B17, SLOT2.B17, SLOT3.B17, SLOT4.B17, U$9.3
LO_RD4: SLOT0.A31, SLOT1.A31, SLOT2.A31, SLOT3.A31, SLOT4.A31, U$16.3
LO_RD5: SLOT0.A32, SLOT1.A32, SLOT2.A32, SLOT3.A32, SLOT4.A32, U$14.3
MEM0: MEM_ID.1, R18.1
MEM1: MEM_ID.2, R17.1
unnamed: LD_0P1.A, R27.2
unnamed: ARCH_ID.5, ARCH_ID.6, ARCH_ID.7, ARCH_ID.8, R122.2
unnamed: MEM_ID.3, MEM_ID.4, R123.2
unnamed: PID.4, PID.5, PID.6, R124.2
unnamed: LD_1P.A, R98.2
unnamed: LD_2P.A, R101.2
unnamed: LD_3P.A, R104.2
unnamed: LD_4P.A, R107.2
PID0: PID.1, R16.1
PID1: PID.2, R15.1
PID2: PID.3, R14.1
S0_PRESENT: R27.1, R61.2, SLOT0.B4
S1_PRESENT: R62.2, R98.1, SLOT1.B4
S2_PRESENT: R63.2, R101.1, SLOT2.B4
S3_PRESENT: R64.2, R104.1, SLOT3.B4
S4_PRESENT: R65.2, R107.1, SLOT4.B4
VALID_RD: SLOT0.A7, SLOT1.A7, SLOT2.A7, SLOT3.A7, SLOT4.A7
VALID_WR: SLOT0.A6, SLOT1.A6, SLOT2.A6, SLOT3.A6, SLOT4.A6
